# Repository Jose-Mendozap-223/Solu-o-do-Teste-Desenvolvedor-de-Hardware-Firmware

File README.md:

# Resolvendo Teste Desenvolvedor-de-Hardware-Firmware
Neste repositório apresenta-se a resposta para o “Teste Situacional - Desenvolvedor de Hardware/Firmware” do candidato Jose Alfredo Mendoza Peñaloza, referente a um projeto de hardware embarcado para a detecção de um sinal externo e, a partir dele, acionar um motor por 10 segundos.

1. Apresentam-se os arquivos Gerber e Drill para visualização no visualizador de sua preferência.
2. Apresentação dos arquivos Pick and Place (PnP), que podem ser visualizados com um leitor de textos.
3. Apresentação do arquivo BOM, que pode ser visualizado com o software Excel.
4. Apresentação do esquema do circuito embarcado em PDF.
5. Apresentação do código em C do projeto para leitura do sinal externo e controle de motor DC, arquivo “Projeto_código.c”.
6. Apresenta-se o documento com as respostas do teste no arquivo: “Teste Situacional - Desenvolvedor de HardwareFirmware_Jose_Mendoza.docx”.
7. Por fim, apresentam-se os arquivos de desenvolvimento do projeto elaborados no KiCad, arquivos: “detetor de sinal 12v.kicad_pcb” e “detetor de sinal 12v.kicad_sch”.

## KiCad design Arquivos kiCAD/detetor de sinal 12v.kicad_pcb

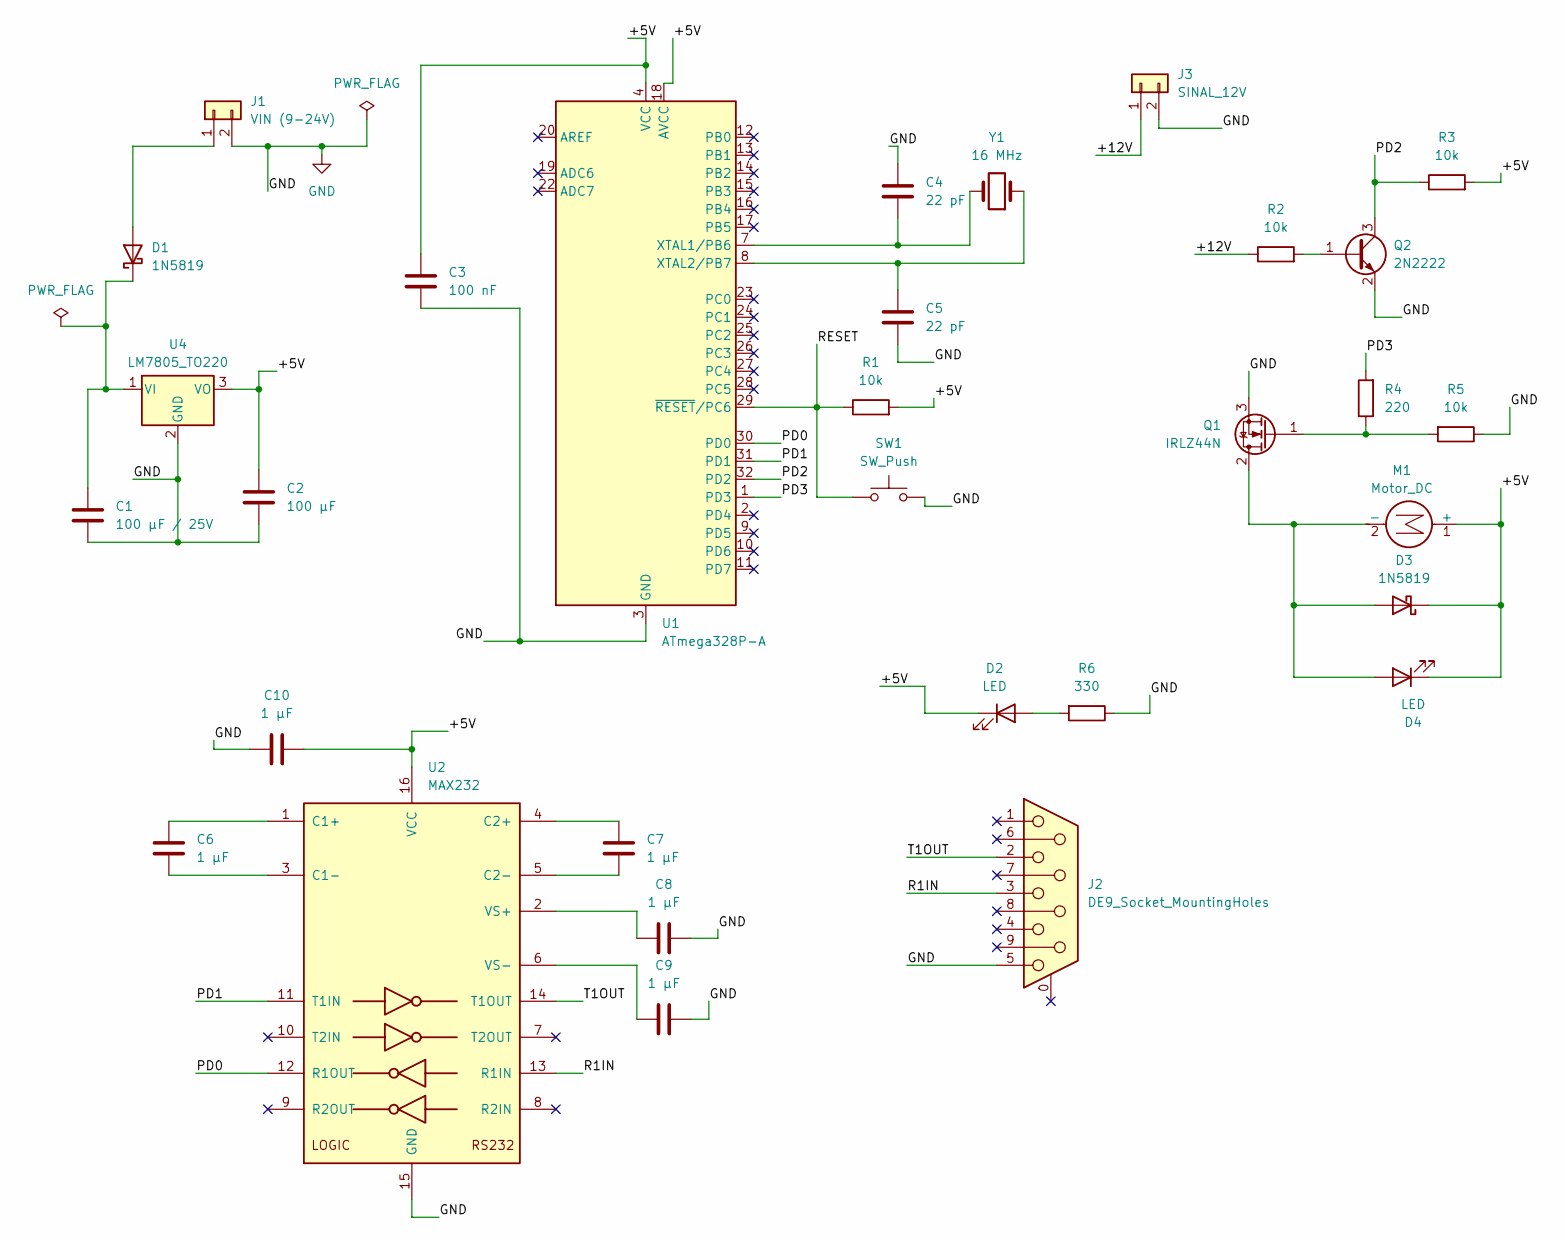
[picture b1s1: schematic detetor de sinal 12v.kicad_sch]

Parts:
C1: 100 µF / 25V; CP_Radial_D5.0mm_P2.50mm
C2: 100 µF; CP_Radial_D5.0mm_P2.50mm
C3: 100 nF; CP_Radial_D5.0mm_P2.50mm
C4, C5: 22 pF; CP_Radial_D5.0mm_P2.50mm
C6, C7, C8, C9, C10: 1 µF; CP_Radial_D5.0mm_P2.50mm
D1, D3: 1N5819; D_DO-41_SOD81_P7.62mm_Horizontal
D2, D4: LED; LED_D5.0mm
J1: VIN (9-24V); TerminalBlock_MaiXu_MX126-5.0-02P_1x02_P5.00mm
J2: DE9_Socket_MountingHoles; DSUB-9_Pins_Horizontal_P2.77x2.84mm_EdgePinOffset14.56mm_Ho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
J3: SINAL_12V; TerminalBlock_MaiXu_MX126-5.0-02P_1x02_P5.00mm
M1: Motor_DC; PinHeader_1x02_P2.54mm_Vertical
Q1: IRLZ44N; TO-220-3_Vertical
Q2: 2N2222; TO-92_Inline
R1, R2, R3, R5: 10k; R_Axial_DIN0207_L6.3mm_D2.5mm_P7.62mm_Horizontal
R4: 220; R_Axial_DIN0207_L6.3mm_D2.5mm_P7.62mm_Horizontal
R6: 330; R_Axial_DIN0207_L6.3mm_D2.5mm_P7.62mm_Horizontal
SW1: SW_Push; SW_PUSH_6mm_H5mm
U1: ATmega328P-A; TQFP-32_7x7mm_P0.8mm
U2: MAX232; DIP-16_W7.62mm
U4: LM7805_TO220; TO-220-3_Vertical
Y1: 16 MHz; Crystal_HC49-U_Vertical

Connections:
/+5V: C2.1, C3.1, C10.2, D2.1 (K), D3.1 (K), D4.1 (K), M1.1 (+), R1.2, R3.2, U1.4 (VCC), U1.6 (VCC), U1.18 (AVCC), U2.16 (VCC), U4.3 (VO)
/+12V: J3.1, R2.1
/PD0: U1.30 (PD0), U2.12 (R1OUT)
/PD1: U1.31 (PD1), U2.11 (T1IN)
/PD2: Q2.3 (C), R3.1, U1.32 (PD2)
/PD3: R4.2, U1.1 (PD3)
/R1IN: J2.3, U2.13 (R1IN)
/RESET: R1.1, SW1.1, U1.29 (~RESET/PC6)
/T1OUT: J2.2, U2.14 (T1OUT)
GND: C1.2, C2.2, C3.2, C4.1, C5.2, C8.2, C9.2, C10.1, J1.2, J2.5, J3.2, Q1.3 (S), Q2.2 (E), R5.1, R6.1, SW1.2, U1.3 (GND), U1.5 (GND), U1.21 (GND), U2.15 (GND), U4.2 (GND)
unnamed: D1.2 (A), J1.1
unnamed: C1.1, D1.1 (K), U4.1 (VI)
unnamed: D2.2 (A), R6.2
unnamed: D3.2 (A), D4.2 (A), M1.2 (-), Q1.2 (D)
unnamed: Q1.1 (G), R4.1, R5.2
unnamed: Q2.1 (B), R2.2
unnamed: C4.2, U1.7 (XTAL1/PB6), Y1.2
unnamed: C5.1, U1.8 (XTAL2/PB7), Y1.1
unnamed: C6.1, U2.1 (C1+)
unnamed: C6.2, U2.3 (C1-)
unnamed: C7.1, U2.4 (C2+)
unnamed: C7.2, U2.5 (C2-)
unnamed: C8.1, U2.2 (VS+)
unnamed: C9.1, U2.6 (VS-)

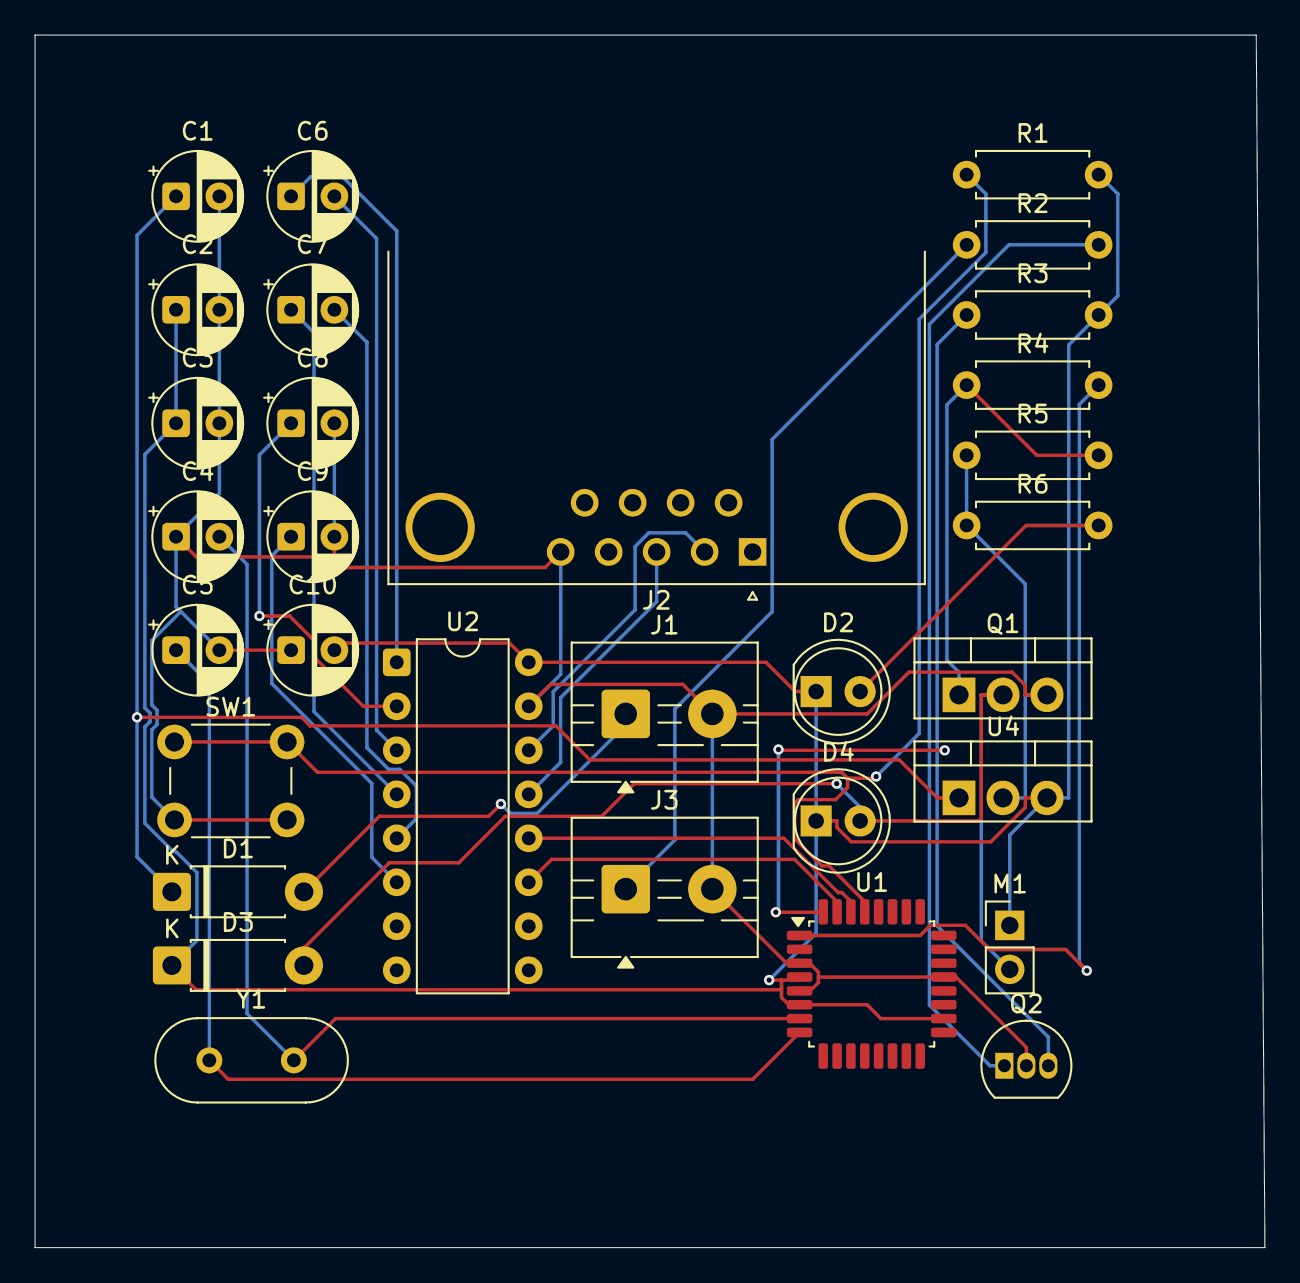
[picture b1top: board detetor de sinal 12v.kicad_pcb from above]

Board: 2 copper layers, 71.0 x 70.0 mm, 31 parts (0 on the bottom side), 24 nets.

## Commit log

2025-10-24 Update README.md
    Atualização README
2025-10-24 Update README.md
    update README v2
2025-10-24 Update project files
